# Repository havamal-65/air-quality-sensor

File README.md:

# Wearable Air Quality Sensor

A small wearable air quality sensor that connects to a phone via Bluetooth Low Energy (BLE). Monitors CO2, particulate matter (PM1.0/PM2.5/PM10), VOCs, NOx, temperature, humidity, and barometric pressure.

## Features

- Real-time CO2 monitoring (400-5000 ppm)
- Particulate matter: PM1.0 / PM2.5 / PM10 (AirSense v4)
- VOC and NOx index detection
- Temperature, humidity, and barometric pressure sensing
- BLE connectivity for mobile app, with on-device history sync (v4)
- Configurable sampling cadence (continuous / 60 s / 300 s / custom, v4)
- OLED display with button-driven pages and cadence menu
- Portable battery power (1-2 day runtime)

## Hardware

### Core Components
- **MCU:** Seeed XIAO ESP32-C3 (RISC-V, BLE 5.0)
- **CO2 Sensor:** Adafruit SCD41 (NDIR CO2 + temp + humidity)
- **VOC Sensor:** Adafruit SGP41 (VOC Index + NOx Index)
- **Display:** SSD1306 OLED 0.96" 128x64 I2C
- **Battery:** LiPo 3.7V 500mAh
- **Total Cost:** ~$109

### I2C Address Map
- SCD41: 0x62
- SGP41: 0x59
- SSD1306: 0x3C

## Project Structure

```
air-quality-sensor/
├── firmware/           # ESP32-C3 firmware (PlatformIO)
│   ├── platformio.ini  #   envs: seeed_xiao_esp32c3 (Phase 2), airsense_v4
│   ├── src/            #   Phase-2 firmware
│   ├── src/v4/         #   AirSense v4: sensor stack, cadence, BLE, OLED UI
│   └── wokwi-v4/       #   v4 simulation: custom chip models, scenarios
├── app/                # Mobile app (React Native / Expo)
│   └── constants/ble-protocol.md  # authoritative v4 BLE contract
├── hardware/           # KiCad projects, PCB docs, BOM
│   ├── kicad_mcp/      #   v3 board (KiCad MCP design iteration)
│   └── v4/             #   AirSense v4 rev B board + fab pack + order BOM
├── scripts/            # ble_verify.py — v4 BLE protocol verification harness
├── enclosure/          # 3D printable case files
└── docs/               # Documentation and wiring diagrams
```

## Getting Started

### Prerequisites

1. Install PlatformIO (VS Code extension or CLI):
   ```bash
   pip install platformio
   ```

2. For mobile app development:
   - React Native: Node.js + Expo CLI
   - OR Flutter: Flutter SDK

### Firmware Development

```bash
cd firmware
pio run -t upload      # Build and upload firmware
pio device monitor     # View serial output
```

### Development Phases

- **Phase 1:** ✅ Basic sensor reading (SCD41) - COMPLETE
- **Phase 2:** ✅ BLE communication with mobile app - COMPLETE
- **Phases 3-5** (VOC sensor, battery power, OLED) are superseded by the
  **AirSense v4** revision below, which delivers all of them plus PM and
  pressure sensing on a custom PCB - design and sim verification COMPLETE
- **Next:** v4 parts order + hardware bring-up, then enclosure design

### Current Status (Phase 2 Complete)

**Working Features:**
- ✅ SCD41 CO2/Temperature/Humidity sensor readings
- ✅ BLE advertising and communication
- ✅ React Native mobile app with Expo SDK 54
- ✅ Real-time data transmission over BLE
- ✅ Web demo deployed to GitHub Pages
- ✅ Web Bluetooth support (Android/Desktop browsers)
- ✅ Historical data charts and alerts
- ✅ Demo mode for testing without hardware
- ✅ Android development build ready

**Technology Stack:**
- Expo SDK 54.0.0
- React Native 0.81.5
- React 19.1.0
- Expo Router 6.0.21
- BLE Library: @sfourdrinier/react-native-ble-plx (RN 0.81 compatible)

**Live Demos:**
- 🌐 **Web App**: https://havamal-65.github.io/air-quality-sensor
  - ✅ Works on Android (Chrome/Edge) with real BLE
  - ✅ Works on Desktop with demo mode
  - ⚠️ iOS Safari: Demo mode only (Apple blocks Web Bluetooth)
- 📱 **Mobile (Expo Go)**: Run `npm start` and scan QR code
  - ✅ Full BLE support on iOS and Android
  - ⚠️ Requires computer running

**How to Use:**

1. **Web Browser (No Install Required)**
   - Open https://havamal-65.github.io/air-quality-sensor on Android Chrome/Edge
   - Tap "Connect Sensor" and select your AirSense device
   - Real-time data appears instantly

2. **Expo Go App (Development)**
   ```bash
   cd app
   npm install
   npm start
   ```
   - Scan QR code with Expo Go app
   - Full native BLE support

3. **Standalone App (Coming Soon)**
   - Build with EAS: `npx eas-cli build --platform ios/android`
   - Install via TestFlight (iOS) or APK (Android)
   - Works anywhere without computer

**Next Steps:**
- Build standalone iOS/Android apps with EAS
- Connect SGP41 VOC/NOx sensor (Phase 3)
- See `firmware/PHASE2-BLE-INSTRUCTIONS.md` for detailed setup

### Hardware Design Status (KiCad MCP, v3 board)

- KiCad project path: `hardware/kicad_mcp/air-quality-sensor-mcp.kicad_pro`
- Schematic: populated and wired (`19` symbols incl. PMSA003I PM sensor and 5 V boost), ERC `0` errors
- PCB: `19` components placed, nets synced (`65` pad nets), routing complete (`160` tracks), DRC `0` errors / `0` warnings
- Manufacturing outputs: Gerbers, drill, BOM, and PnP generated under `hardware/kicad_mcp/manufacturing/`
- Details: `hardware/kicad_mcp/README.md` and `hardware/kicad_mcp/BOARD-DESIGN-NOTES.md`
- Lessons learned: `docs/LESSONS-LEARNED.md`

## AirSense v4 (rev B) — current hardware/firmware track

Full product revision designed and verified 2026-10: custom 100 × 40 mm
2-layer board (ESP32-C3-WROOM-02, SCD41 CO2, SGP41 VOC/NOx, SEN50 PM,
BMP384 pressure, SSD1306 OLED, USB-C, LiPo charge + 5 V boost) with the
firmware, BLE protocol, and verification tooling to match.

**Hardware (`hardware/v4/`)**
- `airsense_v4.kicad_pro/sch/pcb` — DRC-clean board (0 errors), designed
  end to end through KiCad MCP tools with project-local footprints for
  SGP41 and BMP384 (`footprint-verification.md` records the datasheet
  checks; `design-rules.md` records the PCBWay rule set)
- `fab/` — full fab pack: Gerbers (+ PCBWay-profile zip), drill, BOM,
  pick-and-place, STEP model
- `order-bom.md` — priced order list (~$96/device at qty 1, live-priced
  2026-10-13)

**Firmware (`firmware/src/v4/`, PlatformIO env `airsense_v4`)**
- Per-sensor drivers behind one `ISensorDriver` seam, staged warm-up
  scheduler (each sensor gets exactly its own datasheet warm-up), NVS-persisted
  sampling cadence (continuous / 60 s / 300 s / custom 10 s–24 h)
- BLE: serves the frozen Phase-2 contract unchanged, plus v4
  characteristics — pressure, PM (standard + full-resolution custom),
  writable cadence, and a 720-record history ring with framed dump sync.
  Contract documented in `app/constants/ble-protocol.md`
- OLED UI: 4 data pages, button wake/cycle, long-press cadence menu with
  custom-interval submenu, 30 s screen timeout; screen-on or an active BLE
  connection forces continuous sampling, the persisted cadence returns after
- Simulation: `firmware/wokwi-v4/` has custom Wokwi chip models
  (SCD41/SGP41/SEN50/BMP384 register-level, power-pin gated), three scenario
  scripts, OLED screenshot capture, and `check_cadence.py` which verifies
  sample spacing against the firmware's own interval prints

**Verification tooling**
- `scripts/ble_verify.py` — PC-side BLE harness (Python + bleak) asserting
  the whole protocol contract against a live device: GATT table, value
  formats, cadence write/readback, history dump framing, and duty-cadence
  observation via history after a disconnect gap; `--self-test` runs its
  decoder suite with no hardware

**Status:** design, firmware, and simulation verification complete
(schematic → layout → DRC → fab pack; firmware verified in Wokwi:
cadence spacing, NVS persistence across reboot, OLED pages/menu flows,
BLE boot). Next: parts order and hardware bring-up with `ble_verify.py`.

## Air Quality Thresholds

### CO2 Levels
| Level | Range (ppm) | Color | Action |
|-------|-------------|-------|--------|
| Excellent | <600 | Green | None |
| Good | 600-800 | Green | None |
| Moderate | 800-1000 | Yellow | Consider ventilation |
| Poor | 1000-1500 | Orange | Open windows |
| Bad | >1500 | Red | Ventilate immediately |

### VOC Index
| Level | Range | Color | Action |
|-------|-------|-------|--------|
| Good | 0-150 | Green | None |
| Moderate | 150-250 | Yellow | Check for sources |
| Poor | 250-400 | Orange | Ventilate |
| Bad | >400 | Red | Remove source |

## Documentation

See `/docs` for:
- Wiring diagrams
- BOM (Bill of Materials)
- Sensor specifications
- BLE service UUIDs

## Resources

- [SCD41 Datasheet](https://sensirion.com/media/documents/E0F04247/631EF271/CD_DS_SCD40_SCD41_Datasheet_D1.pdf)
- [SGP41 Datasheet](https://sensirion.com/media/documents/5FE8673C/61E96F50/Sensirion_Gas_Sensors_Datasheet_SGP41.pdf)
- [ESP32-C3 Datasheet](https://www.espressif.com/sites/default/files/documentation/esp32-c3_datasheet_en.pdf)

## License

MIT

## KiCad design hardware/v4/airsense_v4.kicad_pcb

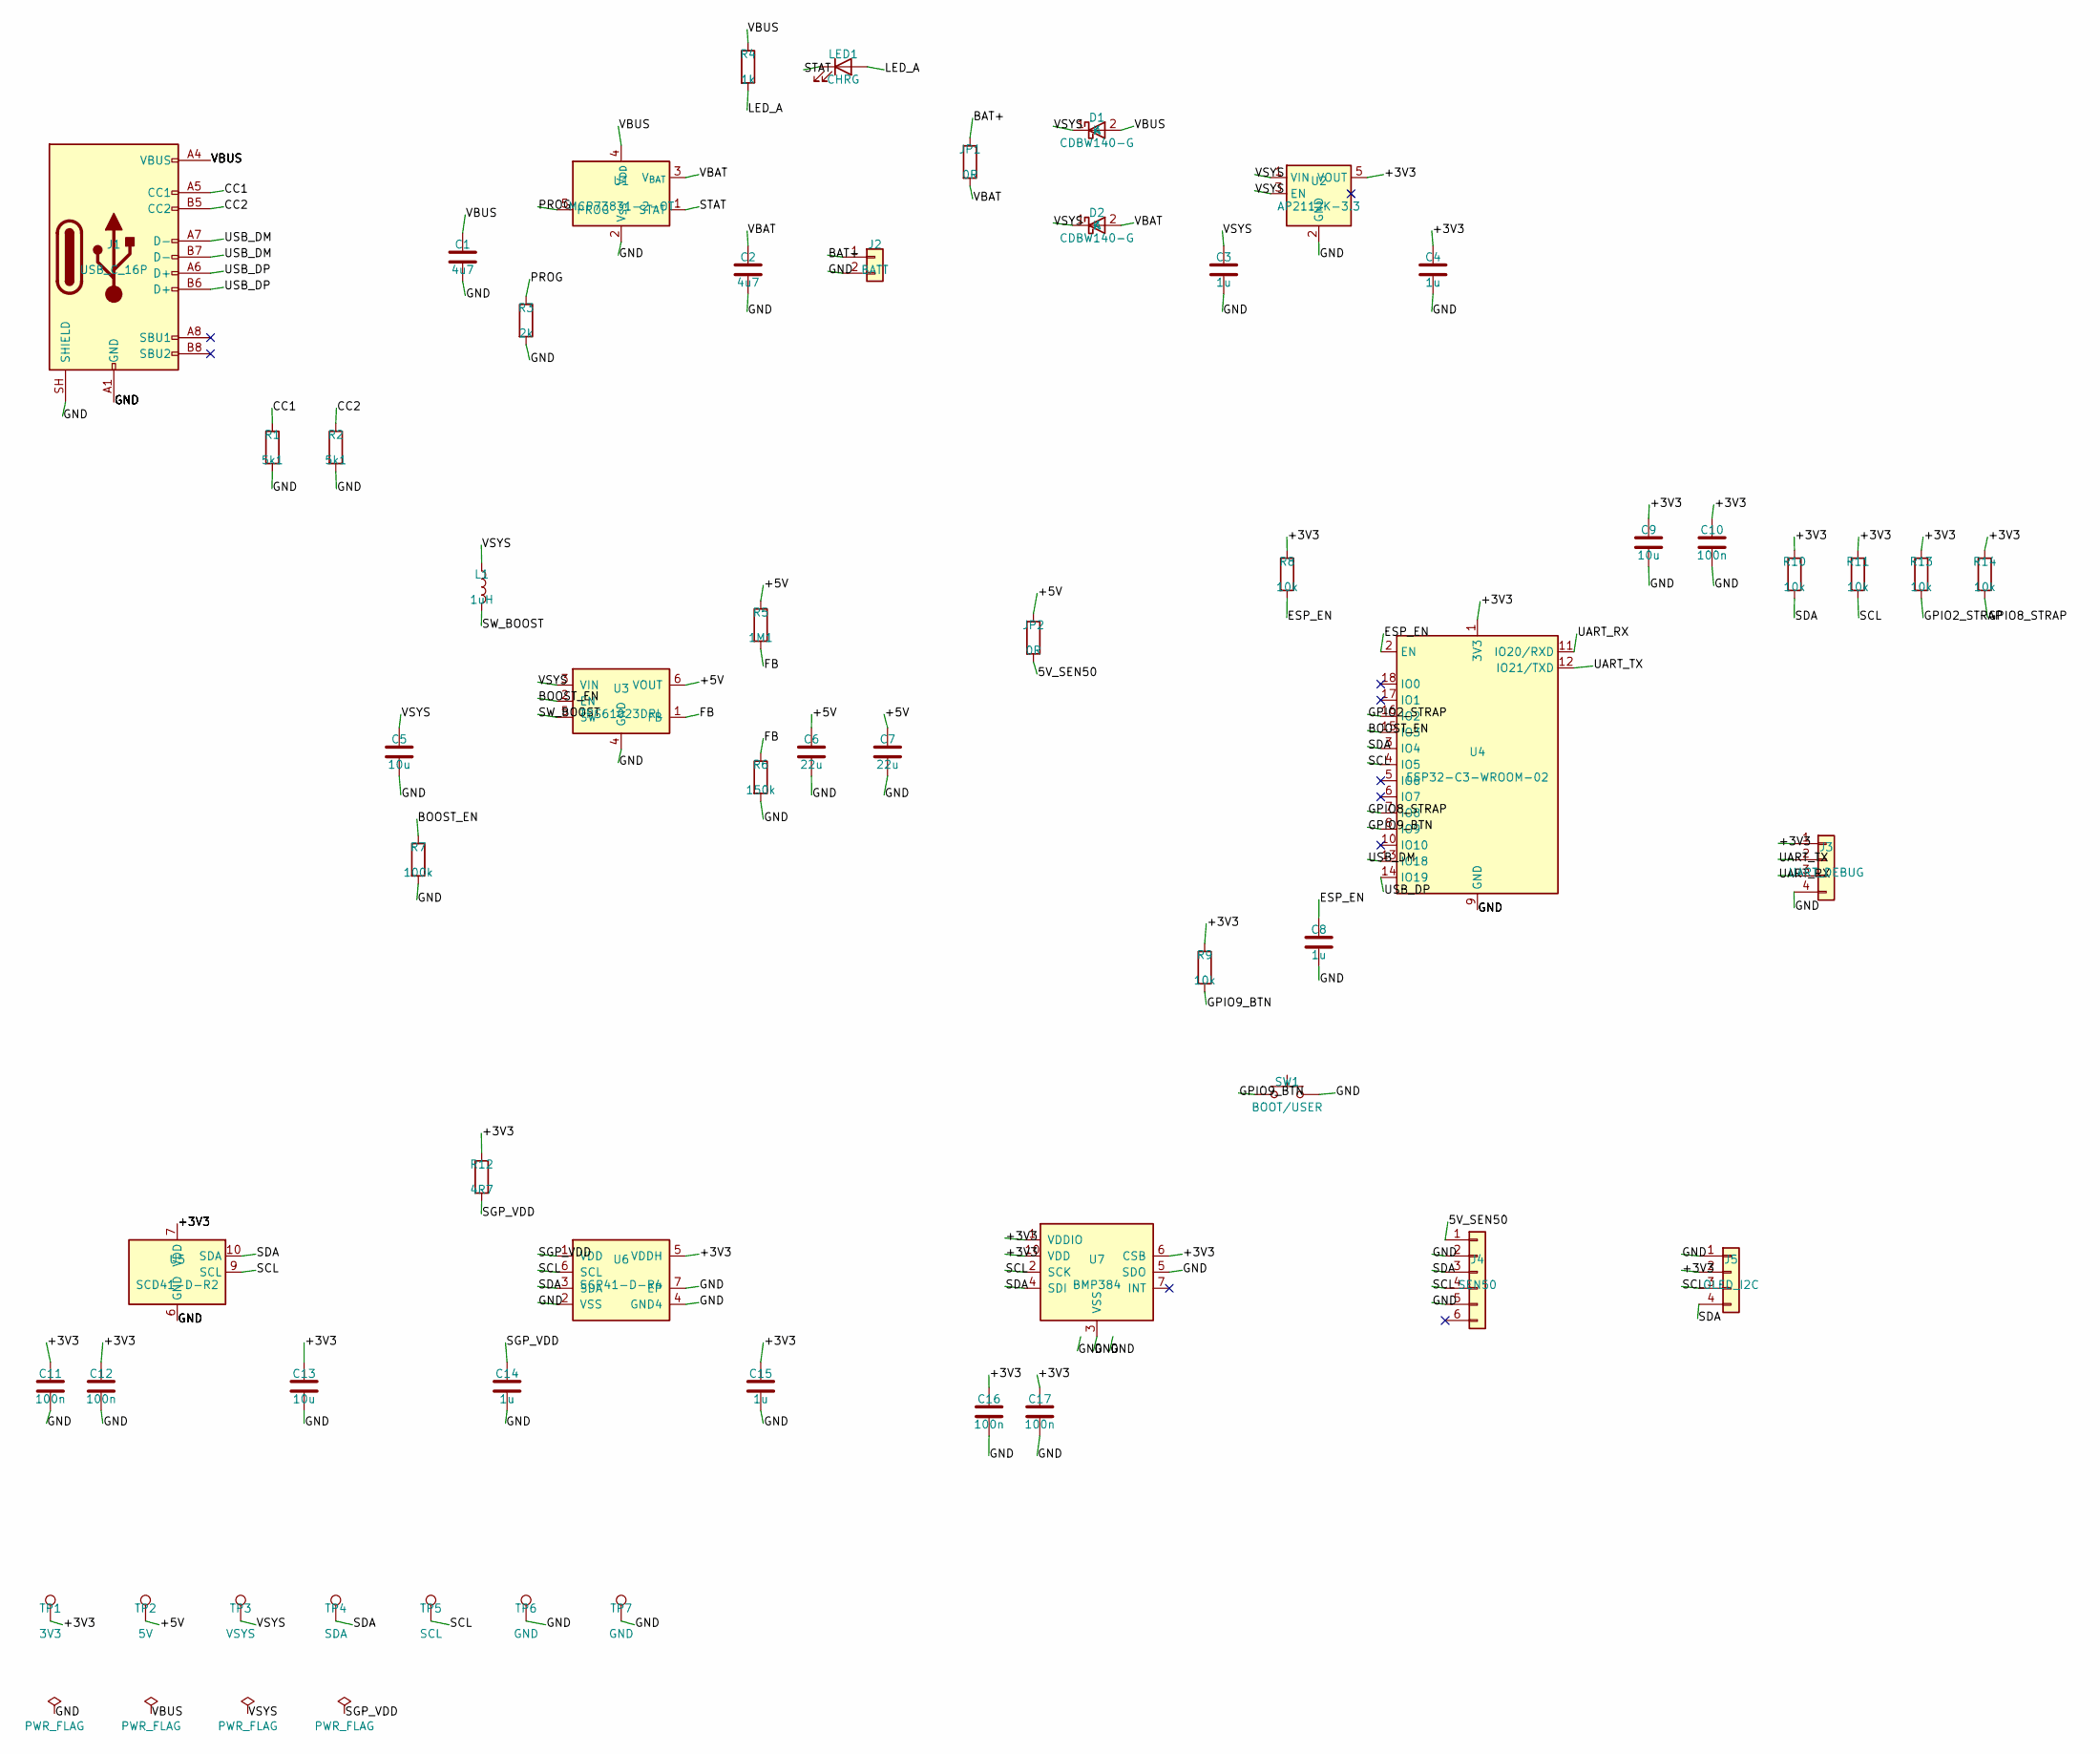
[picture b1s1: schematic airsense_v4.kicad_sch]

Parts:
C1, C2: 4u7; C_0603_1608Metric
C3, C4, C8, C14, C15: 1u; C_0603_1608Metric
C5, C9, C13: 10u; C_0805_2012Metric
C6, C7: 22u; C_0805_2012Metric
C10, C11, C12, C16, C17: 100n; C_0603_1608Metric
D1, D2: CDBW140-G; D_SOD-123
J1: USB_C_16P; USB_C_Receptacle_HRO_TYPE-C-31-M-12
J2: BATT; JST_PH_S2B-PH-SM4-TB_1x02-1MP_P2.00mm_Horizontal
J3: UART_DEBUG; PinHeader_1x04_P2.54mm_Vertical
J4: SEN50; JST_ZH_B6B-ZR-SM4-TF_1x06-1MP_P1.50mm_Vertical
J5: OLED_I2C; PinHeader_1x04_P2.54mm_Vertical
JP1, JP2: 0R; R_0805_2012Metric
L1: 1uH; L_Taiyo-Yuden_NR-40xx
LED1: CHRG; LED_0603_1608Metric
R1, R2: 5k1; R_0603_1608Metric
R3: 2k; R_0603_1608Metric
R4: 1k; R_0603_1608Metric
R5: 1M1; R_0603_1608Metric
R6: 150k; R_0603_1608Metric
R7: 100k; R_0603_1608Metric
R8, R9, R10, R11, R13, R14: 10k; R_0603_1608Metric
R12: 4R7; R_0603_1608Metric
SW1: BOOT/USER; SW_SPST_SKQG_WithStem
TP1: 3V3; TestPoint_Pad_1.5x1.5mm
TP2: 5V; TestPoint_Pad_1.5x1.5mm
TP3: VSYS; TestPoint_Pad_1.5x1.5mm
TP4: SDA; TestPoint_Pad_1.5x1.5mm
TP5: SCL; TestPoint_Pad_1.5x1.5mm
TP6, TP7: GND; TestPoint_Pad_1.5x1.5mm
U1: MCP73831-2-OT; SOT-23-5
U2: AP2112K-3.3; SOT-23-5
U3: TPS61023DRL; SOT-563
U4: ESP32-C3-WROOM-02
U5: SCD41-D-R2; Sensirion_SCD4x-1EP_10.1x10.1mm_P1.25mm_EP4.8x4.8mm
U6: SGP41-D-R4; Sensirion_SGP41_DFN-6-1EP_2.44x2.44mm_P0.8mm
U7: BMP384; Bosch_BMP390_LGA-10_2x2mm

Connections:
/5V_SEN50: J4.1, JP2.2
/+3V3: C4.1, C9.1, C10.1, C11.1, C12.1, C13.1, C15.1, C16.1, C17.1, J3.1, J5.2, R8.1, R9.1, R10.1, R11.1, R12.1, R13.1, R14.1, TP1.1, U2.5 (VOUT), U4.1 (3V3), U5.7 (VDD), U5.19 (VDD), U6.5 (VDDH), U7.1 (VDDIO), U7.6 (CSB), U7.10 (VDD)
/+5V: C6.1, C7.1, JP2.1, R5.1, TP2.1, U3.6 (VOUT)
/BAT+: J2.1, JP1.1
/BOOST_EN: R7.1, U3.2 (EN), U4.15 (IO3)
/CC1: J1.A5 (CC1), R1.1
/CC2: J1.B5 (CC2), R2.1
/ESP_EN: C8.1, R8.2, U4.2 (EN)
/FB: R5.2, R6.1, U3.1 (FB)
/GPIO2_STRAP: R13.2, U4.16 (IO2)
/GPIO8_STRAP: R14.2, U4.7 (IO8)
/GPIO9_BTN: R9.2, SW1.1, U4.8 (IO9)
/LED_A: LED1.2 (A), R4.2
/PROG: R3.1, U1.5 (PROG)
/SCL: J4.4, J5.3, R11.2, TP5.1, U4.4 (IO5), U5.9 (SCL), U6.6 (SCL), U7.2 (SCK)
/SDA: J4.3, J5.4, R10.2, TP4.1, U4.3 (IO4), U5.10 (SDA), U6.3 (SDA), U7.4 (SDI)
/STAT: LED1.1 (K), U1.1 (STAT)
/SW_BOOST: L1.2, U3.5 (SW)
/UART_RX: J3.3, U4.11 (IO20/RXD)
/UART_TX: J3.2, U4.12 (IO21/TXD)
/USB_DM: J1.A7 (D-), J1.B7 (D-), U4.13 (IO18)
/USB_DP: J1.A6 (D+), J1.B6 (D+), U4.14 (IO19)
/VBAT: C2.1, D2.2 (A), JP1.2, U1.3 (V_{BAT})

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
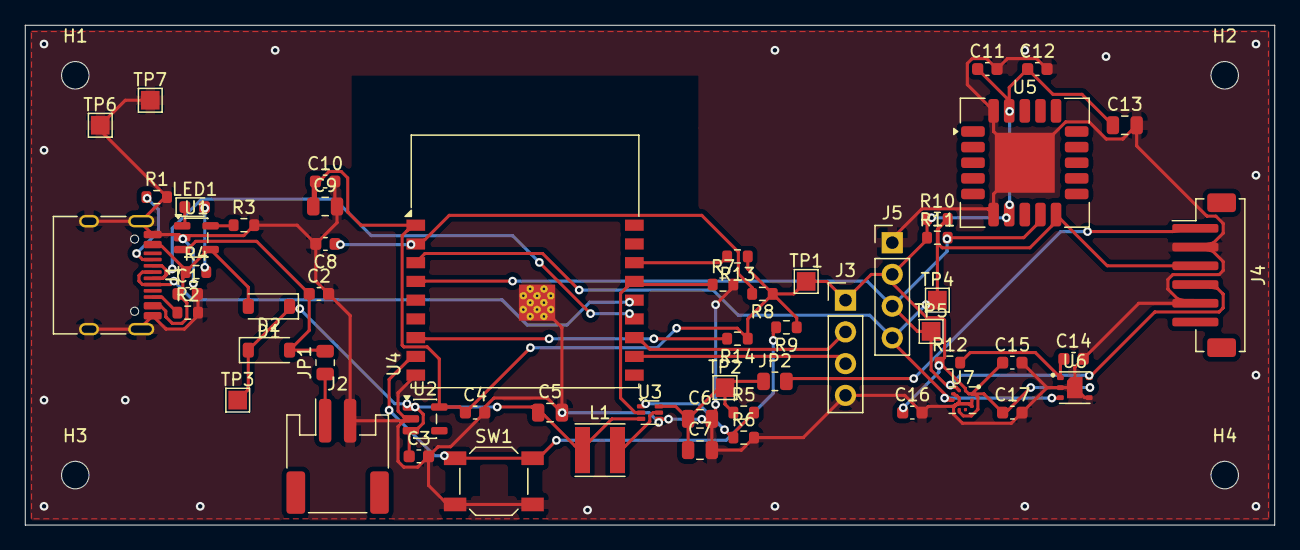
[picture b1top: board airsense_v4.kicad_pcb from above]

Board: 2 copper layers, 100.0 x 40.0 mm, 61 parts (0 on the bottom side), 27 nets.

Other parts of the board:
H1, H2, H3, H4: MountingHole_2.2mm_M2

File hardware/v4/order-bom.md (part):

# AirSense v4 — Order BOM (ticket 04)

**Date of price check:** 2026-10-13 (all prices are live-checked snapshots from
this date; distributor pages cache and change — confirm each line in the cart
before paying).
**Build target:** one staged unit, plus spares on cheap passives and the two
substituted discretes.
**Currency:** USD. Qty-1 prices unless stated.

## Decisions baked into this BOM

1. **BMP384 replaces BMP390** (user decision 2026-10-13). BMP390 is 16-week
   backorder at DigiKey; BMP384 is footprint-, pinout-, and API-identical
   (verified against both datasheets in ticket 01). U7 value updated in the
   schematic and board.
2. **CDBW140-G replaces 1N5819HW-7-F** (D1, D2). The 1N5819HW-7-F is out of
   stock at DigiKey with a 40-week lead; the Comchip CDBW140-G is the same
   class (Schottky, 40 V, 1 A, SOD-123) with ~600 k in stock at $0.16. D1/D2
   values updated in the schematic and board.
3. **NRS4018T1R0NDGJ replaces NR4018T1R0N** (L1). The NR4018 series passed its
   last-time-buy date (2026-03-31); the NRS4018 is Taiyo Yuden's successor in
   the same 4.0 × 4.0 mm land pattern, 1 µH. No design change needed.

## Order 1 — DigiKey

| Ref(s) | Part | MPN | Order qty | Unit price | Line | Stock seen 2026-10-13 |
|---|---|---|---|---|---|---|
| U5 | CO2/T/RH sensor | SCD41-D-R2 | 1 | $21.77 | $21.77 | ~12,956 |
| U6 | VOC/NOx sensor | SGP41-D-R4 | 1 | $9.26 | $9.26 | ~2,639 |
| U7 | Pressure sensor | BMP384 | 2 | $3.52 | $7.04 | ~7,028 |
| — | **PM sensor module** | **SEN50-SDN-T** | 1 | $22.10 | $22.10 | **~300–700 — THIN. ORDER FIRST.** |
| U4 | MCU module | ESP32-C3-WROOM-02-N4 | 2 | $3.38 | $6.76 | ~18,374 |
| U3 | 5 V boost | TPS61023DRLR | 2 | $1.22 | $2.44 | ~24,559 |
| U1 | LiPo charger | MCP73831T-2ACI/OT | 2 | $0.76 | $1.52 | ~33,000+ |
| U2 | 3.3 V LDO | AP2112K-3.3TRG1 | 2 | $0.28 | $0.56 | ~43,000+ |
| D1, D2 | Schottky SOD-123 | CDBW140-G | 10 | $0.099 @10 | $0.99 | ~600,370 |
| L1 | 1 µH 4×4 inductor | NRS4018T1R0NDGJ | 2 | $0.36 | $0.72 | ~4,590 |
| LED1 | 0603 green LED | LTST-C190KGKT | 10 | ~$0.05 @10 | $0.50 | ~148,000 (20-wk mfr lead — buy from stock) |
| J2 | JST PH 2-pin SMT | S2B-PH-SM4-TB(LF)(SN) | 2 | $0.57 | $1.14 | ~14,000 |
| J3, J5 | 1×04 2.54 mm male header | generic breakaway strip (any 1×40, snap to 4) | 2 strips | ~$0.60 | $1.20 | commodity |
| — | 1×04 2.54 mm female socket (OLED mates J5) | PPPC041LFBN-RC | 2 | ~$0.39 | $0.78 | ~6,000 (aggregate) |
| R, C, 0R | passives, see jellybean table below | Yageo RC0603 / CC0603-0805, KEMET/Samsung | 10 of each value (14 values) | ~$0.10 avg | ~$14.00 | commodity |

**DigiKey subtotal ≈ $90.80** (of which spares/stock ≈ $25).

**SEN50 warning (spec flag, re-confirmed 2026-10-13):** DigiKey showed only
~300–700 units (snapshots disagree: 286, 721), Mouser ~107, 5–15 week factory
lead. This is the thin line of the whole build — place the SEN50 order before
or with everything else, not after.

### Passive values (10 pcs each, 0603 unless noted)

Resistors: 5k1 (R1,R2), 2k (R3), 1k (R4), 1M1 (R5), 150k (R6), 100k (R7),
10k (R8–R11,R13,R14), 4R7 (R12).
Capacitors: 100n (C10–C12,C16,C17), 1u (C3,C4,C8,C14,C15), 4u7 (C1,C2),
10u 0805 (C5,C9,C13), 22u 0805 (C6,C7).
Jumpers: 0R 0805 (JP1,JP2).
14 value lines × 10 pcs ≈ $14 at DigiKey catalog cut-tape pricing; the board
consumes 33 of the 140 pieces (≈ $3.30 per device).

## Order 2 — LCSC

The USB-C connector is an LCSC-only part; the ZH connector and switch are
cheapest there, so they ride in the same cart.

| Ref(s) | Part | MPN (LCSC #) | Order qty | Unit price | Line | Stock seen |
|---|---|---|---|---|---|---|
| J1 | USB-C 16P receptacle | TYPE-C-31-M-12 (C165948) | 5 (MOQ) | $0.186 @5 | $0.93 | ~156,000 |
| J4 | JST ZH 6-pin SMT | B6B-ZR-SM4-TFT(LF)(SN) (C265005) | 2 | $0.74 | $1.48 | ~1,570 |
| SW1 | SKQG tactile, with stem | SKQGAFE010 (C202424) | 5 | $0.137 @5 | $0.69 | ~1,000–5,900 |

**LCSC subtotal ≈ $3.10** + shipping (~$7 economy). DigiKey's own listings for
these: B6B-ZR-SM4-TFT no stock / 16-wk, SKQGAFE010 not listed — LCSC is the
in-stock source, not just the cheap one.

## Order 3 — off-distributor items

| Item | Source | Price | Note |
|---|---|---|---|
| 2000 mAh protected LiPo, JST-PH | Adafruit #2011 — **out of stock** ($12.50, notify-me set) → in-stock fallback: Jameco #2507799 | $12.50 / **$16.55** | Protection circuit built in (3.0 V cutout, short protection), genuine JST-PH — both verified on the Adafruit page |
| SSD1306 0.96″ 128×64 I2C OLED module | Amazon/AliExpress multi-pack (e.g. AITRIP 10-pack $22.99) or single ~$3 | ~$2.30–3.00 | Any 4-pin I2C variant (GND-VCC-SCL-SDA); pin order varies by seller — check against J5 before plugging |
| SEN50 cable (ZHR-6, 1.5 mm) | SparkFun "Breadboard to JST-ZHR 6-pin" ×2 | $2.25 ea, $4.50 | Board J4 and the SEN50 both take ZHR-6 housings; two breadboard cables spliced back-to-back make the harness, and the Dupont ends serve bring-up probing first |
| M2 standoff/screw kit (nylon) | Amazon assortment | ~$9 (estimate) | For H1–H4; optional until an enclosure exists |
| Solder stencil (frameless) | PCBWay, added to board order | ~$10–15 | SGP41 needs 125–150 µm foil — note it in the order comments |

## Order 4 — PCBWay boards

Upload `fab/airsense_v4_pcbway_gerbers.zip` (12 files: 2× copper, 2× mask,
2× silk, 2× paste, edge cuts, PTH + NPTH drill, job file) to the PCBWay quote
tool. Settings: 2 layers, 100 × 40 mm, FR-4 1.6 mm, HASL or ENIG, 5 pcs
(smallest tier). Indicative 2026 pricing: boards ~$5–10 / 5 pcs, stencil
~$10–15, shipping ~$15–20 → **~$30–45 landed** with stencil. The design rules
were written against PCBWay's standard 2-layer limits (see `design-rules.md`),
so no special options are needed.

## Per-device parts cost (AC-15, BOM half)

One assembled device, at the qty-1 prices above:

| Block | Cost |
|---|---|
| Sensors (SCD41 + SGP41 + BMP384 + SEN50) | $56.65 |
| MCU module | $3.38 |
| Power ICs + diodes + inductor (U1–U3, D1–D2, L1) | $2.82 |
| Connectors + switch + LED (J1–J5, SW1, LED1, socket) | $3.23 |
| Passives consumed (33 pcs) | $3.30 |
| OLED module | $3.00 |
| Battery (in-stock price) | $16.55 |
| Board share (5-board order ÷ 5, incl. stencil + ship) | ~$7.00 |
| **Per-device total** | **≈ $96** |

Consistent with the spec's ~$100 estimate. The recurring (board-revision) cost
is the board share plus passives — the sensors, modules, battery, and OLED all
carry over on connectors or get reflowed once.

## Price sources (checked 2026-10-13)

- [SCD41-D-R2 — DigiKey](https://www.digikey.com/en/products/detail/sensirion-ag/SCD4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
- [SGP41-D-R4 — DigiKey](https://www.digikey.com/en/products/detail/sensirion-ag/SGP4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
- [BMP384 — DigiKey](https://www.digikey.com/en/products/detail/bosch-sensortec/B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
- [SEN50-SDN-T — DigiKey](https://www.digikey.com/en/products/detail/sensirion-ag/SEN5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
- [ESP32-C3-WROOM-02-N4 — DigiKey](https://www.digikey.com/en/products/detail/espressif-systems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
- [TPS61023DRLR — DigiKey](https://www.digikey.com/en/products/detail/texas-instruments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
- [MCP73831T-2ACI/OT — DigiKey](https://www.digikey.com/en/products/detail/microchip-technol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
- [AP2112K-3.3TRG1 — DigiKey](https://www.digikey.com/en/products/detail/diodes-incorporat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
- [CDBW140-G — DigiKey](https://www.digikey.com/en/products/detail/comchip-technolog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
- [1N5819HW-7-F (backordered original) — DigiKey](https://www.digikey.com/en/products/detail/diodes-incorporat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
- [NRS4018T1R0NDGJ — distributor aggregate](https://electronicsdatasheets.com/manufacturers/taiyo-yuden/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
- [LTST-C190KGKT — DigiKey](https://www.digikey.co.nz/en/products/detail/liteon/LTST-C19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
- [TYPE-C-31-M-12 — LCSC C165948](https://lcsc.com/product-detail/C165948.html)
- [B6B-ZR-SM4-TFT — LCSC C265005](https://www.lcsc.com/product-image/C265005.html)
- [SKQGAFE010 — LCSC C202424](https://www.lcsc.com/product-image/C202424.html)
- [S2B-PH-SM4-TB — DigiKey via aggregate](https://www.flux.ai/lcsc/s2b-ph-sm4-tblfsn.md)
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
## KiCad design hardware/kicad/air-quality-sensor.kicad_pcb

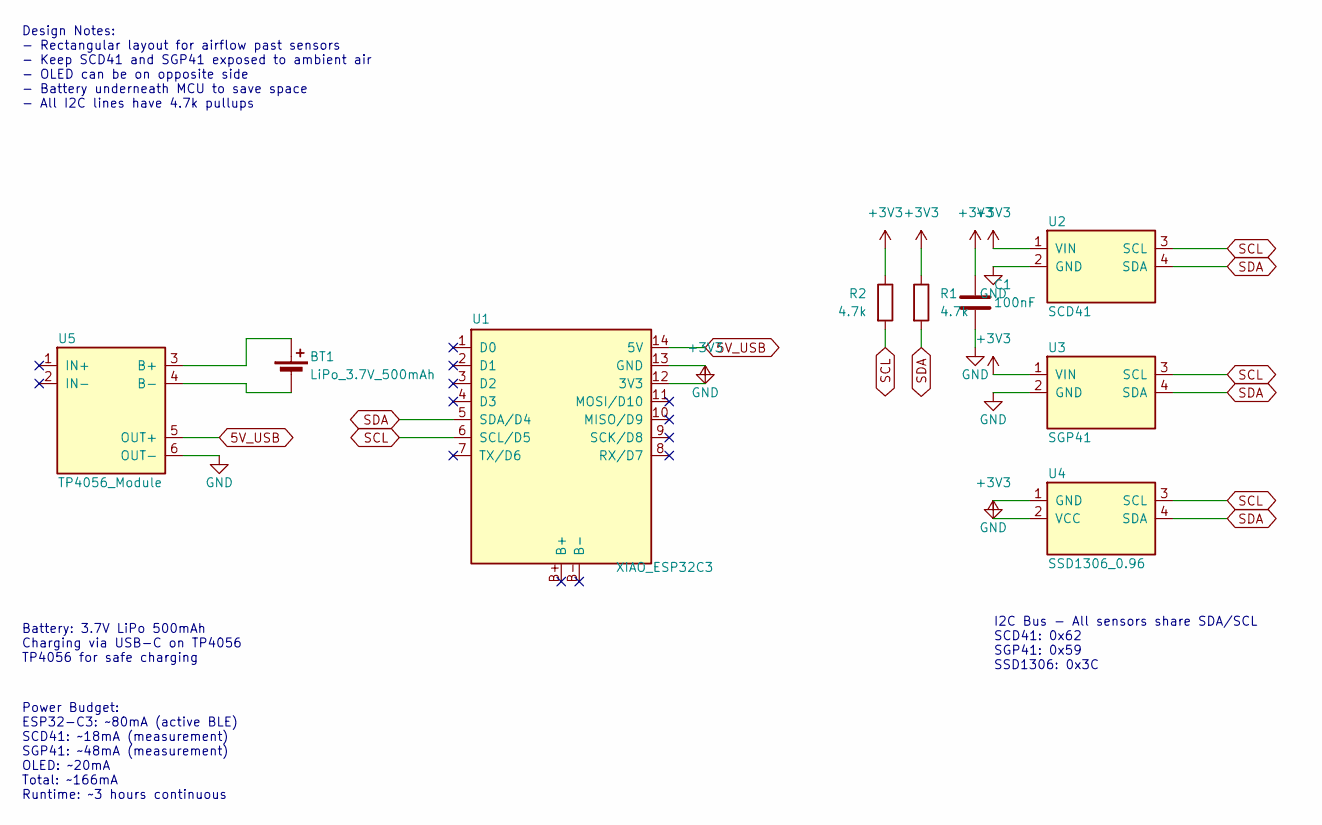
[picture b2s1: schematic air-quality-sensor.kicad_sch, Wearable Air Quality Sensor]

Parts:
BT1: LiPo_3.7V_500mAh; JST_PH_2pin_Battery
C1: 100nF; C_0603_1608Metric
R1, R2: 4.7k; R_0603_1608Metric
U1: XIAO_ESP32C3
U2: SCD41; Adafruit_SCD41
U3: SGP41; Adafruit_SGP41
U4: SSD1306_0.96; SSD1306_OLED_128x64
U5: TP4056_Module; TP4056_USB-C_Module

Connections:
5V_USB: U1.14 (5V), U5.5 (OUT+)
+3V3: C1.1, R1.1, R2.1, U1.12 (3V3), U2.1 (VIN), U3.1 (VIN), U4.2 (VCC)
GND: C1.2, U1.13 (GND), U2.2 (GND), U3.2 (GND), U4.1 (GND), U5.6 (OUT-)
unnamed: BT1.1 (+), U5.3 (B+)
unnamed: BT1.2 (-), U5.4 (B-)
SCL: R2.2, U1.6 (SCL/D5), U2.3 (SCL), U3.3 (SCL), U4.3 (SCL)
SDA: R1.2, U1.5 (SDA/D4), U2.4 (SDA), U3.4 (SDA), U4.4 (SDA)

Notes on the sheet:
I2C Bus - All sensors share SDA/SCL SCD41: 0x62 SGP41: 0x59 SSD1306: 0x3C
Battery: 3.7V LiPo 500mAh Charging via USB-C on TP4056 TP4056 for safe charging
Power Budget: ESP32-C3: ~80mA (active BLE) SCD41: ~18mA (measurement) SGP41: ~48mA (measurement) OLED: ~20mA Total: ~166mA Runtime: ~3 hours continuous
Design Notes: - Rectangular layout for airflow past sensors - Keep SCD41 and SGP41 exposed to ambient air - OLED can be on opposite side - Battery underneath MCU to save space - All I2C lines have 4.7k pullups

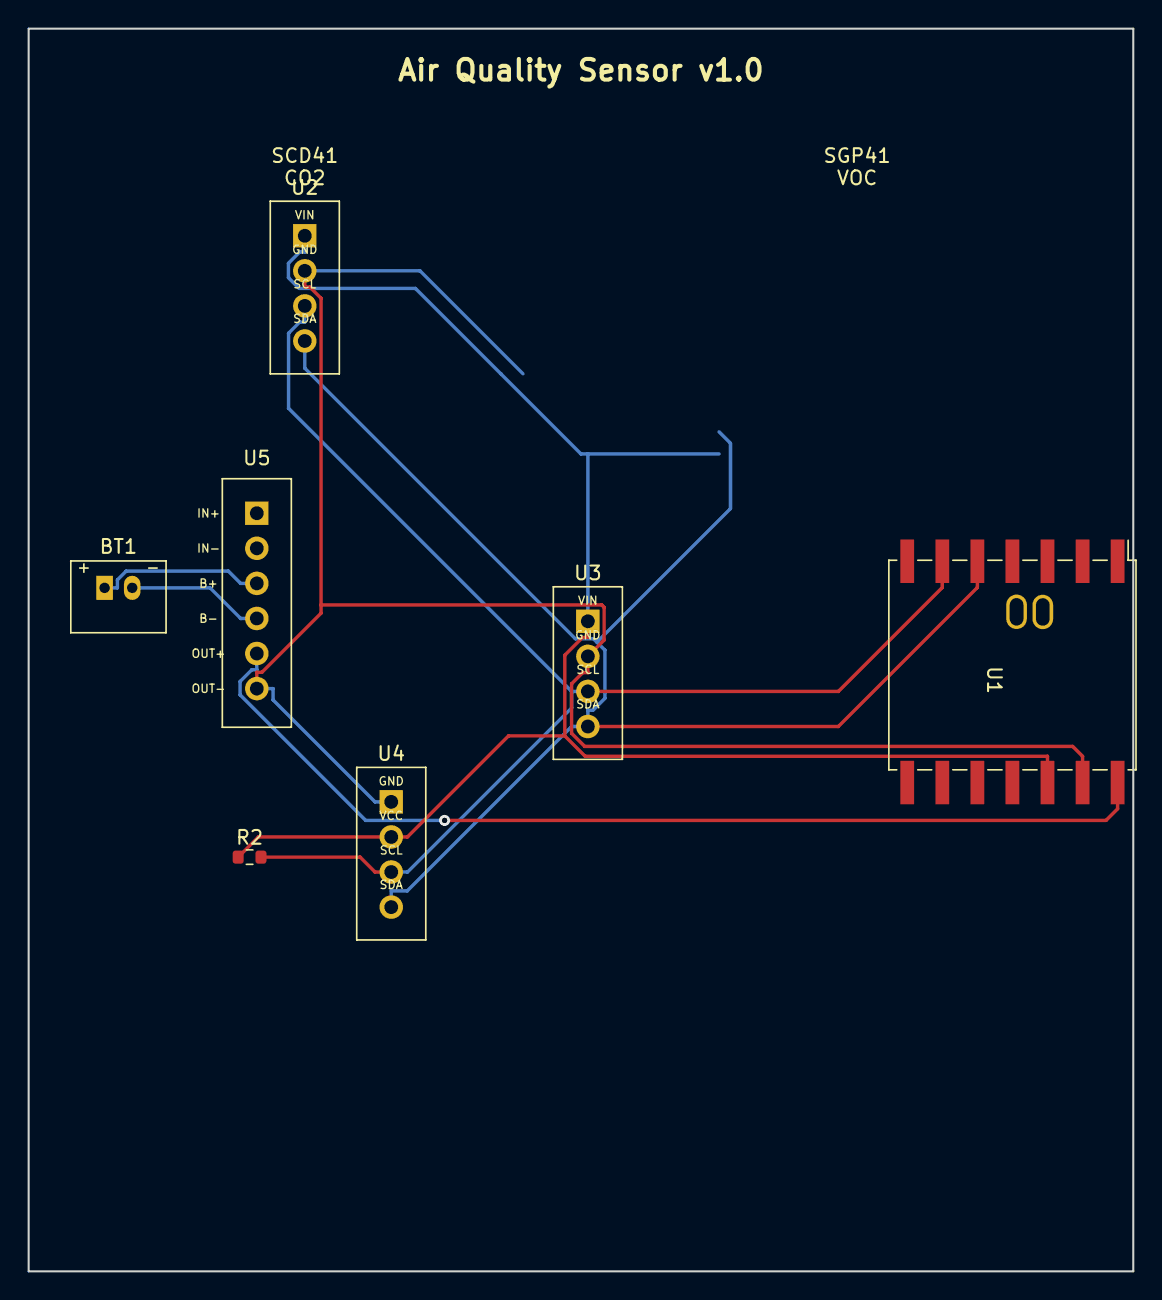
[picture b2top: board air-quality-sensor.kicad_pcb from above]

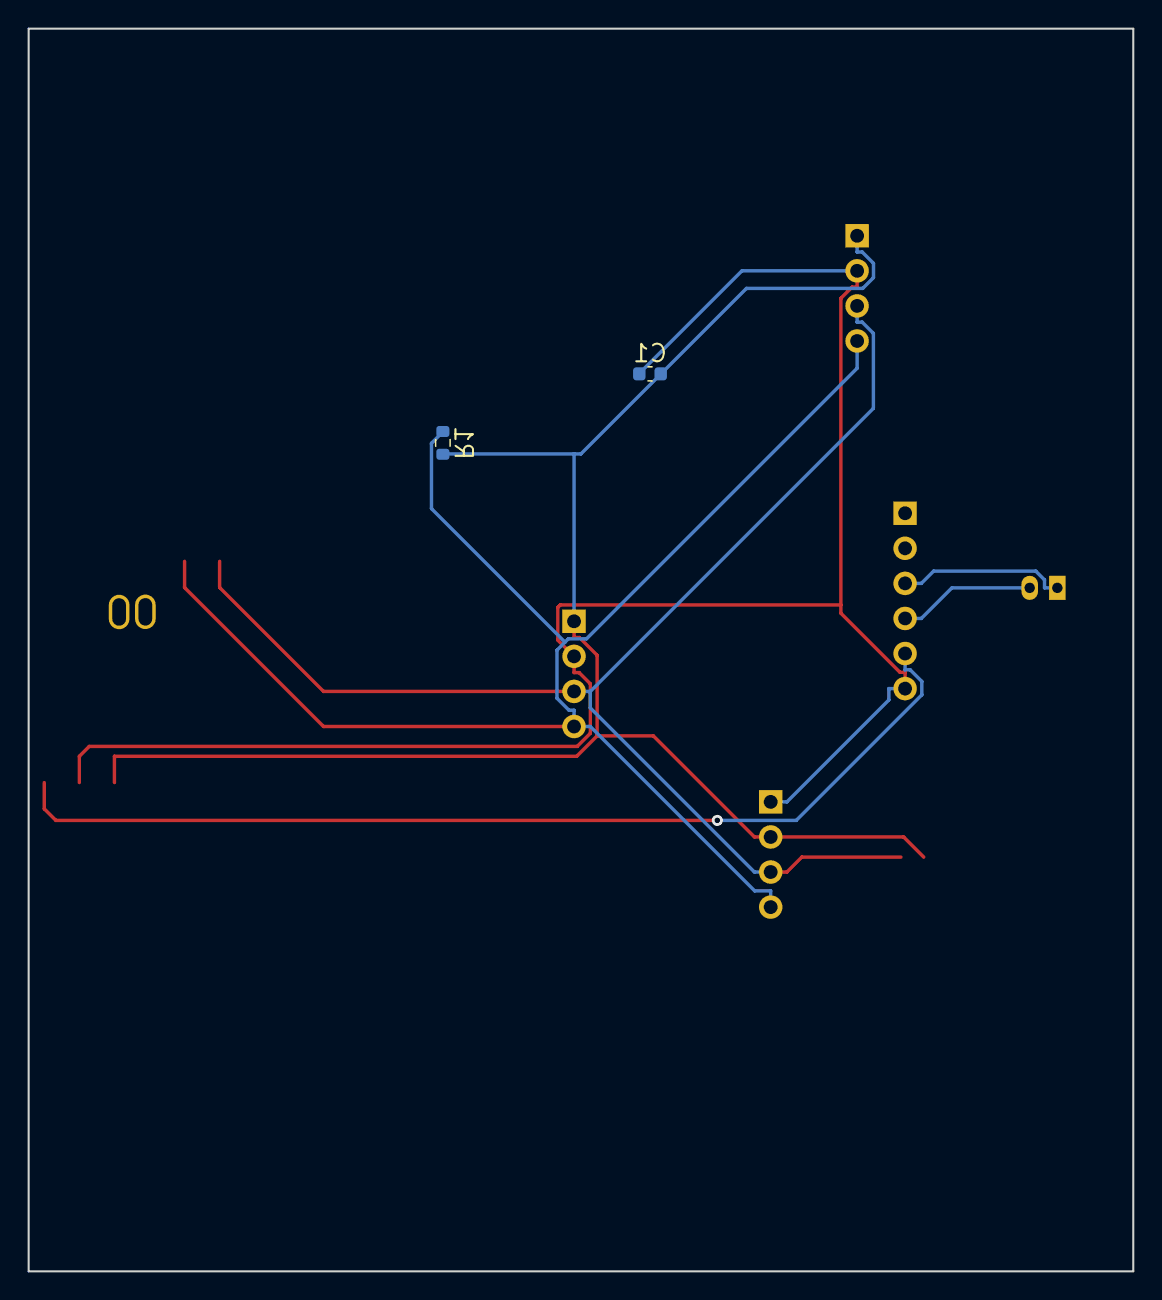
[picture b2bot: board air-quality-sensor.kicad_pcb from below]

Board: 2 copper layers, 80.0 x 90.0 mm, 9 parts (2 on the bottom side), 7 nets.

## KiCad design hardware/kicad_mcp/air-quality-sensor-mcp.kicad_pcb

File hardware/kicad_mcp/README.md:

# KiCad MCP Design

This directory contains the KiCad MCP design iteration for this project (updated 2026-02-23).

## Primary files
- `air-quality-sensor-mcp.kicad_pro`
- `air-quality-sensor-mcp.kicad_sch`
- `air-quality-sensor-mcp.kicad_pcb`
- `sym-lib-table`
- `fp-lib-table`

## Validation outputs
- `mcp_build_summary.json` - initial PCB placement summary
- `mcp_schematic_build_summary.json` - schematic build + ERC + schematic/PCB compare summary
- `erc-mcp-validation.json` - latest ERC report from MCP `run_erc`
- `drc-mcp-validation.json` - latest DRC report from MCP `run_drc`
- `MCP-FUTURE-CHANGES.md` - MCP-only remediation backlog and validation baseline

## Current status
- Schematic populated and wired (`19` placed symbols), ERC `0` errors (`7` cosmetic off-grid warnings on the D1/U7 auto-stubs)
- Components: U1 XIAO ESP32-C3 (**through-hole DIP** footprint for soldered header pins), U2 SCD41, U3 SGP41, U4 SSD1306, U5 TP4056, **U6 Adafruit PMSA003I PM2.5**, **U7 5 V boost (TPS61023-class)**, **D1 Schottky (SS14)**, J1 JST-PH, R1/R2 I²C pull-ups, R3/R4, C1–C4, LED1/LED2
- Power tree (battery-only wearable): LiPo → TP4056 (charge) → `VBAT` → U7 boost → `+5V` → { PMSA003I `VIN` ; D1 Schottky → XIAO `5V` pin }. Sensors/OLED on `+3V3` from the XIAO regulator. XIAO `B+`/`B-` no-connect (unreachable on header pins)
- Schematic/PCB consistency: `19/19` present, `0` footprint mismatches. Cosmetic only: D1/U6/U7 PCB `Value` fields show the placed footprint name (autoroute SES-import resets them); the schematic + BOM carry the real part names — so the **BOM is generated from the schematic**
- PCB nets synced from schematic via MCP (`65` pad net assignments)
- PCB routing completed via MCP auto-routing (`160` routed tracks); DRC clean (`0` errors / `0` warnings, `0` unconnected, `0` schematic-parity); `0` courtyard overlaps. U1 through-hole DIP confirmed on the board (41 THT pads total incl. U1's 14)
- Manufacturing outputs regenerated via MCP:
  - `manufacturing/gerbers/` (incl. NPTH + PTH drills for the through-hole pins)
  - `manufacturing/drill/`
  - `manufacturing/air-quality-sensor-mcp-bom.csv` (from schematic)
  - `manufacturing/air-quality-sensor-mcp-pnp.csv`
- See `BOARD-DESIGN-NOTES.md` for board-specific status/open items (incl. the U1 footprint-swap method via direct board edit). MCP tooling issues hit during this work are tracked in the KiCad-MCP repo: `D:\GitHub\KiCad-MCP\MCP-KNOWN-ISSUES.md`.

## Open in KiCad
```powershell
"C:\Program Files\KiCad\9.0\bin\kicad.exe" "D:\GitHub\Portfolio\Projects\air-quality-sensor\hardware\kicad_mcp\air-quality-sensor-mcp.kicad_pro"
```

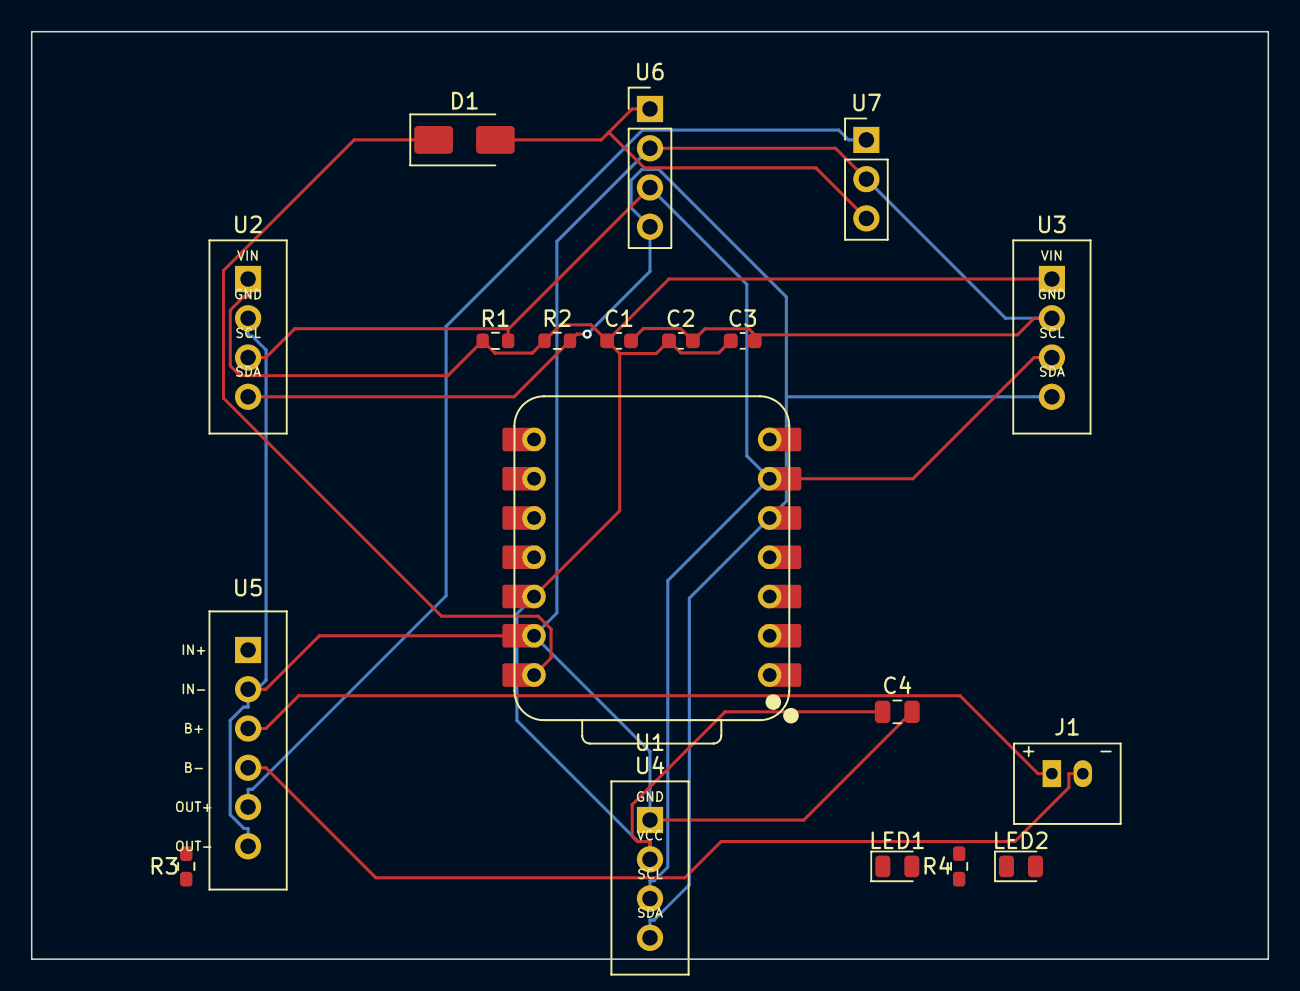
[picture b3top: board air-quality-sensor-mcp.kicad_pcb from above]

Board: 2 copper layers, 80.0 x 60.0 mm, 19 parts (0 on the bottom side), 9 nets.

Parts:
C1, C2, C3: 100nF; C_0603_1608Metric
C4: 10uF; C_0805_2012Metric
D1: D_SMA
J1: JST_PH_2pin_Battery
LED1: RED; LED_0805_2012Metric
LED2: GREEN; LED_0805_2012Metric
R1, R2: 4.7k; R_0603_1608Metric
R3: 1.2k; R_0603_1608Metric
R4: 1k; R_0603_1608Metric
U1: XIAO_ESP32C3; XIAO-ESP32C3-DIP
U2: Adafruit_SCD41
U3: Adafruit_SGP41
U4: SSD1306_OLED_128x64
U5: TP4056_USB-C_Module
U6: PinHeader_1x04_P2.54mm_Vertical
U7: PinHeader_1x03_P2.54mm_Vertical

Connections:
+3V3: C1.1, C2.1, C3.1, C4.1, R1.1, R2.1, U1.12, U2.1, U3.1, U4.2
+5V: D1.2, U6.1, U7.3
BAT+: J1.1, U5.3
BAT-: J1.2, U5.4
GND: C1.2, C2.2, C3.2, C4.2, U1.13, U2.2, U3.2, U4.1, U5.2, U5.6, U6.2, U7.2
I2C_SCL: R1.2, U1.6, U2.3, U3.3, U4.3, U6.3
I2C_SDA: R2.2, U1.5, U2.4, U3.4, U4.4, U6.4
VBAT: U5.5, U7.1
XIAO_5V: D1.1, U1.14

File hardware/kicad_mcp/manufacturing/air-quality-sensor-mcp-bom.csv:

"Refs","Value","Footprint","Qty","DNP"
"C1","100nF","Capacitor_SMD:C_0603_1608Metric","1",""
"C2","100nF","Capacitor_SMD:C_0603_1608Metric","1",""
"C3","100nF","Capacitor_SMD:C_0603_1608Metric","1",""
"C4","10uF","Capacitor_SMD:C_0805_2012Metric","1",""
"D1","SS14","Diode_SMD:D_SMA","1",""
"J1","JST_PH_2pin_Battery","AirQuality:JST_PH_2pin_Battery","1",""
"LED1","RED","LED_SMD:LED_0805_2012Metric","1",""
"LED2","GREEN","LED_SMD:LED_0805_2012Metric","1",""
"R1","4.7k","Resistor_SMD:R_0603_1608Metric","1",""
"R2","4.7k","Resistor_SMD:R_0603_1608Metric","1",""
"R3","1.2k","Resistor_SMD:R_0603_1608Metric","1",""
"R4","1k","Resistor_SMD:R_0603_1608Metric","1",""
"U1","XIAO_ESP32C3","Seeed_XIAO:XIAO-ESP32C3-DIP","1",""
"U2","Adafruit_SCD41","AirQuality:Adafruit_SCD41","1",""
"U3","Adafruit_SGP41","AirQuality:Adafruit_SGP41","1",""
"U4","SSD1306_OLED_128x64","AirQuality:SSD1306_OLED_128x64","1",""
"U5","TP4056_USB-C_Module","AirQuality:TP4056_USB-C_Module","1",""
"U6","Adafruit_PMSA003I","Connector_PinHeader_2.54mm:PinHeader_1x04_P2.54mm_Vertical","1",""
"U7","Boost_5V_TPS61023","Connector_PinHeader_2.54mm:PinHeader_1x03_P2.54mm_Vertical","1",""

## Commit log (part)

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2026-01-13 Add Web Bluetooth support for browser testing
2026-01-14 Fix React Native Text component and deploy to GitHub Pages
2026-01-14 Update documentation: SDK 54 upgrade, Web Bluetooth, standalone app guide
2026-01-14 Remove temp files
2026-01-14 Update README: User-focused instructions for using the app
2026-01-15 Revert iOS changes - keeping original repo unchanged
2026-02-21 Add KiCad MCP hardware design docs and lessons learned
2026-02-22 Rewire MCP schematic visibly and refresh hardware docs
2026-02-22 Limit latest update scope to MCP files only
2026-02-24 Finalize MCP demo board, docs, and manufacturing outputs
